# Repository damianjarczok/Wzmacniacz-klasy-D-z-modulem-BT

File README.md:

Wzmacniacz audio klasy D 2.1 oparty na TPA3116D2, z filtrem dolnoprzepustowym Sallen-Key, regulacją barwy (Baxandall), zasilaniem 24 V, interfejsem Bluetooth 4.2 (MH-M18) i wejściem AUX. Projekt PCB 4-warstwowy z filtracją EMI i optymalizacją ścieżek sygnałowych.

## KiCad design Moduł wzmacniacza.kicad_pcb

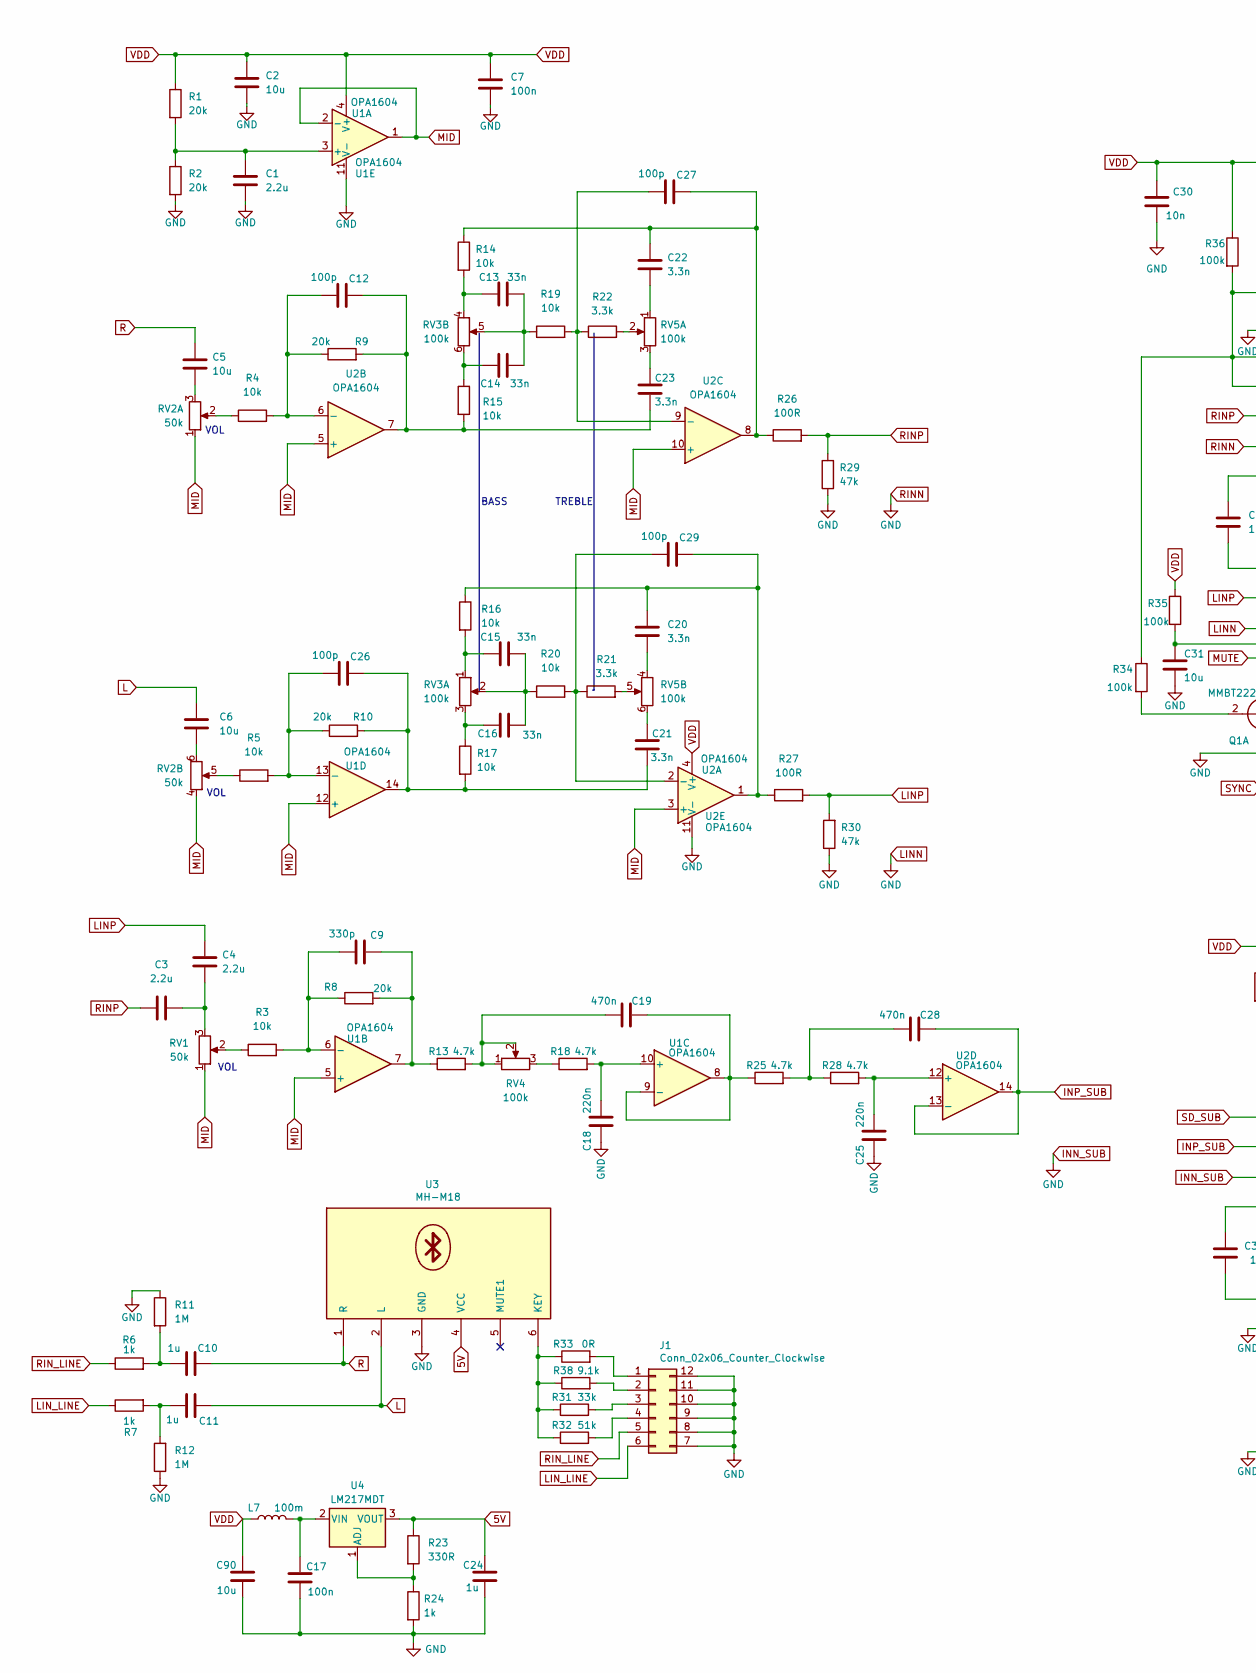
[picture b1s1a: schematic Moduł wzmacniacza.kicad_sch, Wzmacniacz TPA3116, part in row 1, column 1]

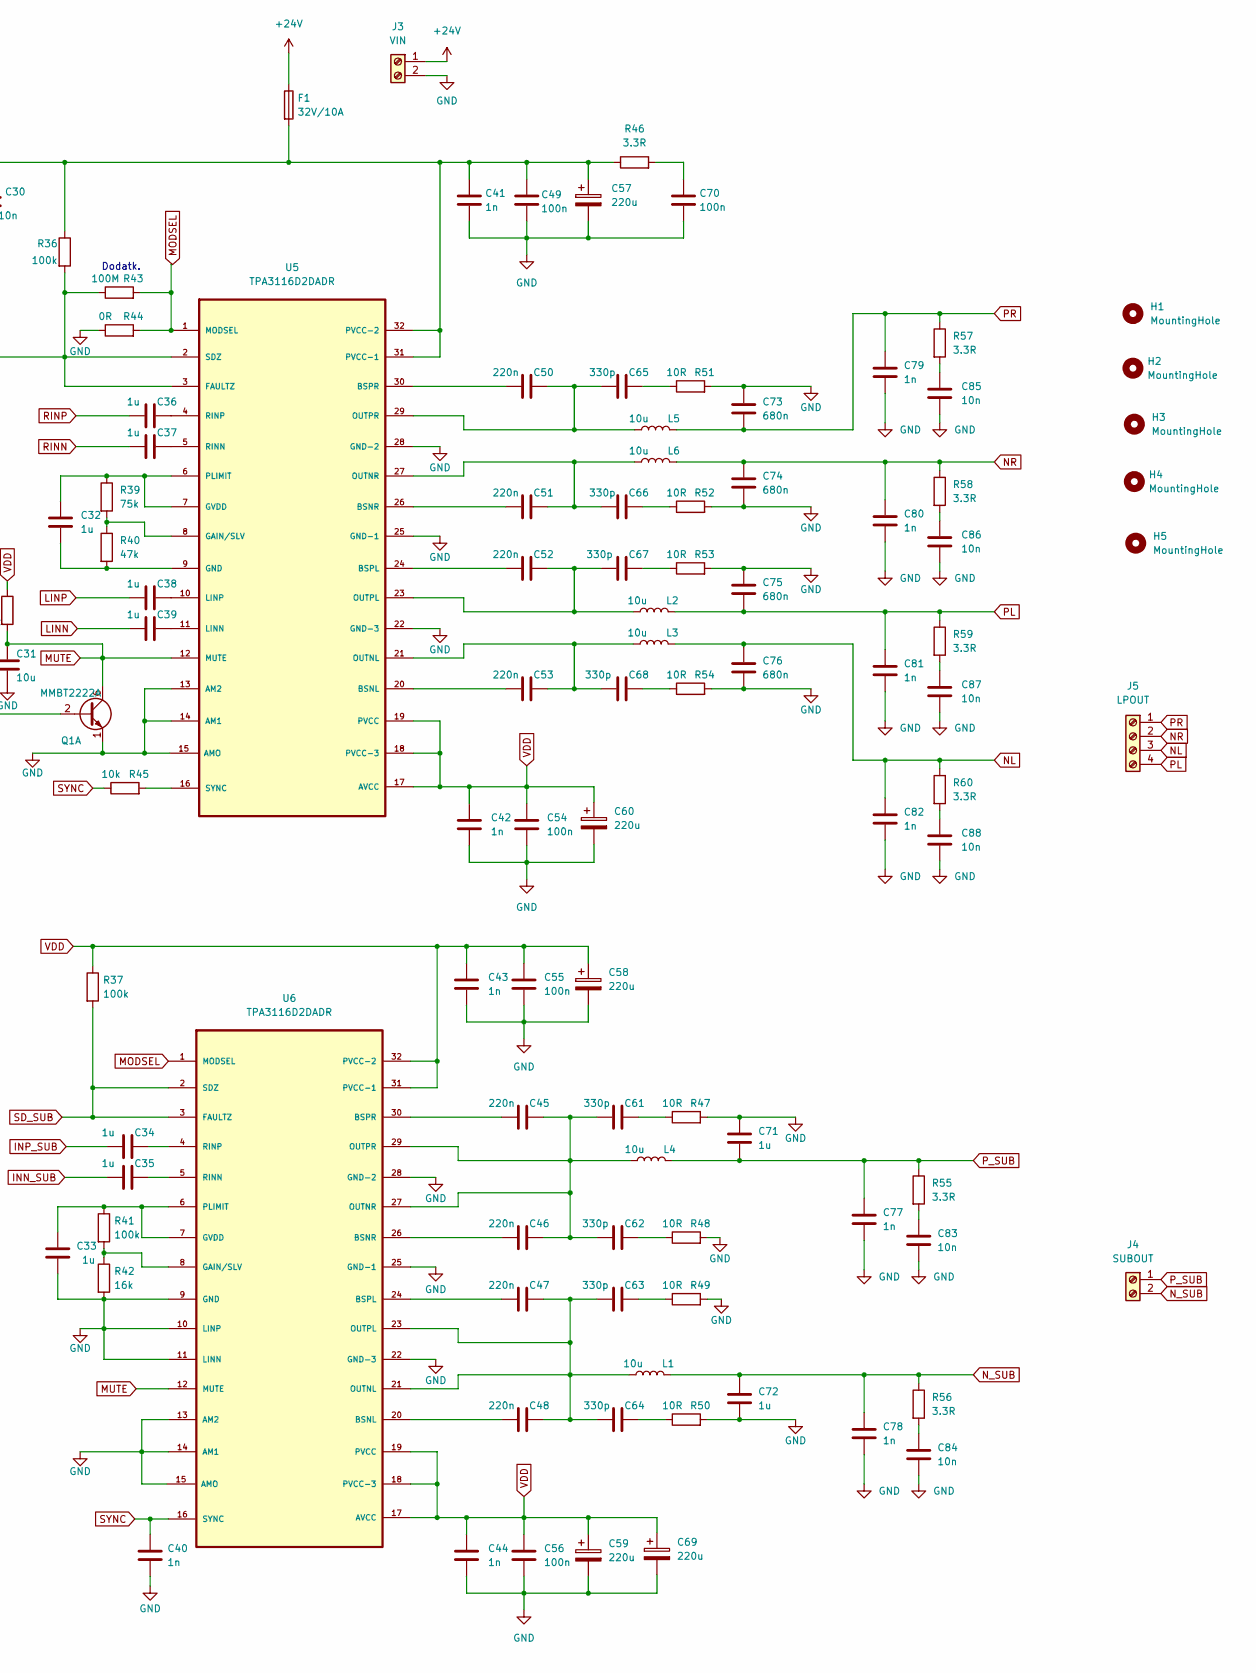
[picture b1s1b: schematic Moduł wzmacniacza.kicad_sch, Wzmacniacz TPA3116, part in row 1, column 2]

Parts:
C1, C3, C4: 2.2u; C_1206_3216Metric
C2, C5, C6, C31: 10u; C_1210_3225Metric
C7, C17, C49, C54, C55, C56, C70: 100n; C_1206_3216Metric
C9, C61, C62, C63, C64, C65, C66, C67, C68: 330p; C_0805_2012Metric
C10, C11, C34, C35, C36, C37, C38, C39, C71, C72: 1u; C_2220_5650Metric
C12, C26, C27, C29: 100p; C_0805_2012Metric
C13, C14, C15, C16: 33n; C_0805_2012Metric
C18, C25, C45, C46, C47, C48, C50, C51, C52, C53: 220n; C_0805_2012Metric
C19, C28: 470n; C_0805_2012Metric
C20, C21, C22, C23: 3.3n; C_0805_2012Metric
C24, C32, C33: 1u; C_1206_3216Metric
C30, C83, C84, C85, C86, C87, C88: 10n; C_1206_3216Metric
C40, C41, C42, C43, C44, C77, C78, C79, C80, C81, C82: 1n; C_0805_2012Metric
C57, C58, C59, C60, C69: 220u; CP_Elec_10x10
C73, C74, C75, C76: 680n; C_1206_3216Metric
C90: 10u; C_1206_3216Metric
F1: 32V/10A; Fuse
H1, H2, H3, H4, H5: MountingHole; MountingHole_3.2mm_M3_DIN965_Pad
J1: Conn_02x06_Counter_Clockwise; IDC-Header_2x06_P2.54mm_Vertical
J3: VIN; Screw 2
J4: SUBOUT; Screw 2
J5: LPOUT; Screw 4
L1, L2, L3, L4, L5, L6: 10u; Dlawik
L7: 100m; L_1812_4532Metric
Q1: MMBT2222A; SOT-23
R1, R2, R8, R9, R10: 20k; R_0805_2012Metric
R3, R4, R5, R14, R15, R16, R17, R19, R20, R45: 10k; R_0805_2012Metric
R6, R7, R24: 1k; R_0805_2012Metric
R11, R12: 1M; R_0805_2012Metric
R13, R18, R25, R28: 4.7k; R_0805_2012Metric
R21, R22: 3.3k; R_0805_2012Metric
R23: 330R; R_0805_2012Metric
R26, R27: 100R; R_0805_2012Metric
R29, R30, R40: 47k; R_0805_2012Metric
R31: 33k; R_0805_2012Metric
R32: 51k; R_0805_2012Metric
R33, R44: 0R; R_0805_2012Metric
R34, R35, R36, R37, R41: 100k; R_0805_2012Metric
R38: 9.1k; R_0805_2012Metric
R39: 75k; R_0805_2012Metric
R42: 16k; R_0805_2012Metric
R43: 100M; R_0805_2012Metric
R46, R55, R56, R57, R58, R59, R60: 3.3R; R_0805_2012Metric
R47, R48, R49, R50, R51, R52, R53, R54: 10R; R_0805_2012Metric
RV1: 50k; Pot single
RV2: 50k; Pot dual
RV3, RV5: 100k; Pot dual
RV4: 100k; Pot single
U1, U2: OPA1604; SOIC-14_3.9x8.7mm_P1.27mm
U3: MH-M18; BM20
U4: LM217MDT; TO-252-2
U5, U6: TPA3116D2DADR; HTSSOP-32-1EP_6.1x11mm_P0.65mm_EP5.2x11mm_Mask4.11x4.36mm

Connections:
5V: C24.1, R23.1, U3.4 (VCC), U4.3 (VOUT)
+24V: F1.1, J3.1
INN_SUB: C1.2, C2.2, C7.2, C17.2, C18.1, C24.2, C25.1, C30.2, C31.2, C33.2, C35.1, C37.1, C39.1, C40.2, C41.2, C42.2, C43.2, C44.2, C49.2, C54.2, C55.2, C56.2, C57.2, C58.2, C59.2, C60.2, C69.2, C70.2, C71.1, C72.2, C73.1, C74.2, C75.1, C76.2, C77.2, C78.2, C79.2, C80.2, C81.2, C82.2, C83.2, C84.2, C85.2, C86.2, C87.2, C88.2, C90.2, H1.1, H2.1, H3.1, H4.1, H5.1, J1.7, J1.8, J1.9, J1.10, J1.11, J1.12, J3.2, Q1.1 (E1), R2.2, R11.1, R12.1, R24.2, R29.1, R30.1, R42.2, R44.1, R47.2, R48.2, R49.2, R50.2, R51.2, R52.2, R53.2, R54.2, U1.11 (V-), U2.11 (V-), U3.3 (GND), U5.13 (AM2), U5.14 (AM1), U5.15 (AMO), U5.22 (GND-3), U5.25 (GND-1), U5.28 (GND-2), U5.33, U6.9 (GND), U6.10 (LINP), U6.11 (LINN), U6.13 (AM2), U6.14 (AM1), U6.15 (AMO), U6.22 (GND-3), U6.25 (GND-1), U6.28 (GND-2), U6.33
INP_SUB: C28.2, C34.1, U2.13 (-), U2.14
L: C6.1, C11.2, U3.2 (L)
LINP: C4.1, C38.1, R27.2, R30.2
LIN_LINE: J1.6, R7.1
MID: RV1.1, RV2.1, RV2.4, U1.1, U1.2 (-), U1.5 (+), U1.12 (+), U2.3 (+), U2.5 (+), U2.10 (+)
MODSEL: R43.2, R44.2, U5.1 (MODSEL), U6.1 (MODSEL)
MUTE: C31.1, Q1.6 (C1), R35.2, U5.12 (MUTE), U6.12 (MUTE)
NL: C76.1, C82.1, J5.3, L3.2, R60.1
NR: C74.1, C80.1, J5.2, L6.2, R58.1
N_SUB: C72.1, C78.1, J4.2, L1.2, R56.1
unnamed: C1.1, R1.2, R2.1, U1.3 (+)
unnamed: C3.2, C4.2, RV1.3
unnamed: C5.2, RV2.3
unnamed: C6.2, RV2.6
unnamed: C9.1, R3.2, R8.1, U1.6 (-)
unnamed: C9.2, R8.2, R13.1, U1.7
unnamed: C10.1, R6.2, R11.2
unnamed: C11.1, R7.2, R12.2
unnamed: C12.1, R4.2, R9.1, U2.6 (-)
unnamed: C12.2, C23.2, R9.2, R15.2, U2.7
unnamed: C13.1, R14.2, RV3.4
unnamed: C13.2, C14.2, R19.1, RV3.5
unnamed: C14.1, R15.1, RV3.6
unnamed: C15.1, R16.2, RV3.1
unnamed: C15.2, C16.2, R20.1, RV3.2
unnamed: C16.1, R17.1, RV3.3
unnamed: C17.1, L7.1, U4.2 (VIN)
unnamed: C18.2, R18.2, U1.10 (+)
unnamed: C19.1, R13.2, RV4.1, RV4.2
unnamed: C19.2, R25.1, U1.8, U1.9 (-)
unnamed: C20.1, C29.2, R16.1, R27.1, U2.1
unnamed: C20.2, RV5.4
unnamed: C21.1, RV5.6
unnamed: C21.2, C26.2, R10.2, R17.2, U1.14
unnamed: C22.1, C27.2, R14.1, R26.1, U2.8
unnamed: C22.2, RV5.1
unnamed: C23.1, RV5.3
unnamed: C25.2, R28.2, U2.12 (+)
unnamed: C26.1, R5.2, R10.1, U1.13 (-)
unnamed: C27.1, R19.2, R22.1, U2.9 (-)
unnamed: C28.1, R25.2, R28.1
unnamed: C29.1, R20.2, R21.1, U2.2 (-)
unnamed: C32.1, R39.1, U5.6 (PLIMIT), U5.7 (GVDD)
unnamed: C32.2, R40.2, U5.9 (GND)
unnamed: C33.1, R41.1, U6.6 (PLIMIT), U6.7 (GVDD)
unnamed: C34.2, U6.4 (RINP)
unnamed: C35.2, U6.5 (RINN)
unnamed: C36.2, U5.4 (RINP)
unnamed: C37.2, U5.5 (RINN)
unnamed: C38.2, U5.10 (LINP)
unnamed: C39.2, U5.11 (LINN)
unnamed: C45.1, U6.30 (BSPR)
unnamed: C45.2, C46.2, C61.1, C62.1, L4.1, U6.27 (OUTNR), U6.29 (OUTPR)
unnamed: C46.1, U6.26 (BSNR)
unnamed: C47.1, U6.24 (BSPL)
unnamed: C47.2, C48.2, C63.1, C64.1, L1.1, U6.21 (OUTNL), U6.23 (OUTPL)
unnamed: C48.1, U6.20 (BSNL)
unnamed: C50.1, U5.30 (BSPR)
unnamed: C50.2, C65.1, L5.1, U5.29 (OUTPR)
unnamed: C51.1, U5.26 (BSNR)
unnamed: C51.2, C66.1, L6.1, U5.27 (OUTNR)
unnamed: C52.1, U5.24 (BSPL)
unnamed: C52.2, C67.1, L2.1, U5.23 (OUTPL)
unnamed: C53.1, U5.20 (BSNL)
unnamed: C53.2, C68.1, L3.1, U5.21 (OUTNL)
unnamed: C61.2, R47.1
unnamed: C62.2, R48.1
unnamed: C63.2, R49.1
unnamed: C64.2, R50.1
unnamed: C65.2, R51.1
unnamed: C66.2, R52.1
unnamed: C67.2, R53.1
unnamed: C68.2, R54.1
unnamed: C70.1, R46.2
unnamed: C83.1, R55.2
unnamed: C84.1, R56.2
unnamed: C85.1, R57.2
unnamed: C86.1, R58.2
unnamed: C87.1, R59.2
unnamed: C88.1, R60.2
unnamed: J1.1, R33.2
unnamed: J1.2, R38.2
unnamed: J1.3, R31.2
unnamed: J1.4, R32.2
unnamed: Q1.2 (B1), R34.2
unnamed: R3.1, RV1.2
unnamed: R4.1, RV2.2
unnamed: R5.1, RV2.5
unnamed: R18.1, RV4.3
unnamed: R21.2, RV5.5
unnamed: R22.2, RV5.2
unnamed: R23.2, R24.1, U4.1 (ADJ)
unnamed: R31.1, R32.1, R33.1, R38.1, U3.6 (KEY)
unnamed: R34.1, R36.2, R43.1, U5.2 (SDZ), U5.3 (FAULTZ)
unnamed: R39.2, R40.1, U5.8 (GAIN/SLV)
unnamed: R41.2, R42.1, U6.8 (GAIN/SLV)
unnamed: R45.2, U5.16 (SYNC)
PL: C75.2, C81.1, J5.4, L2.2, R59.1
PR: C73.2, C79.1, J5.1, L5.2, R57.1
P_SUB: C71.2, C77.1, J4.1, L4.2, R55.1
R: C5.1, C10.2, U3.1 (R)
RINP: C3.1, C36.1, R26.2, R29.2
RIN_LINE: J1.5, R6.1
SD_SUB: R37.2, U6.2 (SDZ), U6.3 (FAULTZ)
SYNC: C40.1, R45.1, U6.16 (SYNC)
VDD: C2.1, C7.1, C30.1, C41.1, C42.1, C43.1, C44.1, C49.1, C54.1, C55.1, C56.1, C57.1, C58.1, C59.1, C60.1, C69.1, C90.1, F1.2, L7.2, R1.1, R35.1, R36.1, R37.1, R46.1, U1.4 (V+), U2.4 (V+), U5.17 (AVCC), U5.18 (PVCC-3), U5.19 (PVCC), U5.31 (PVCC-1), U5.32 (PVCC-2), U6.17 (AVCC), U6.18 (PVCC-3), U6.19 (PVCC), U6.31 (PVCC-1), U6.32 (PVCC-2)

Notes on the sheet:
VOL
TREBLE
Dodatk.
BASS

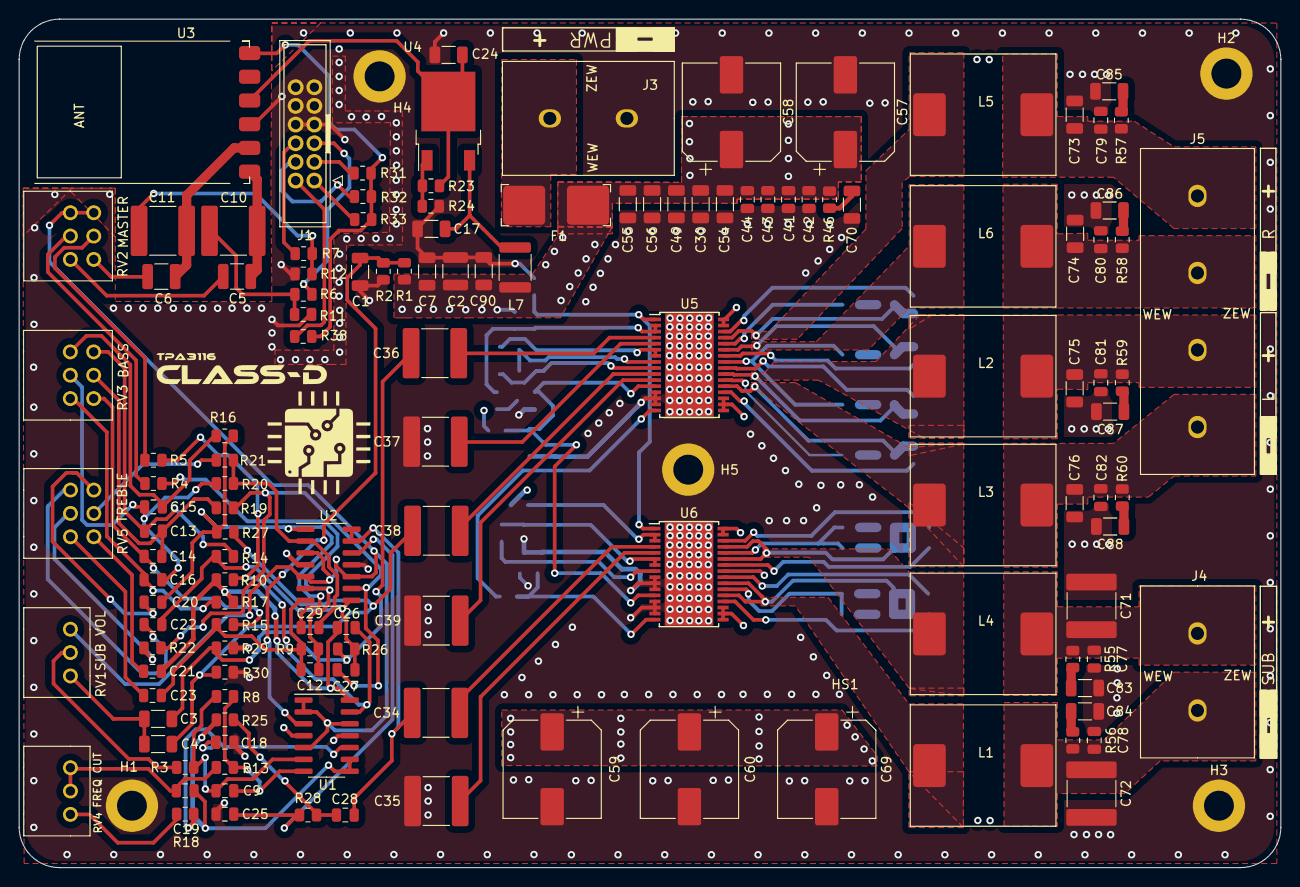
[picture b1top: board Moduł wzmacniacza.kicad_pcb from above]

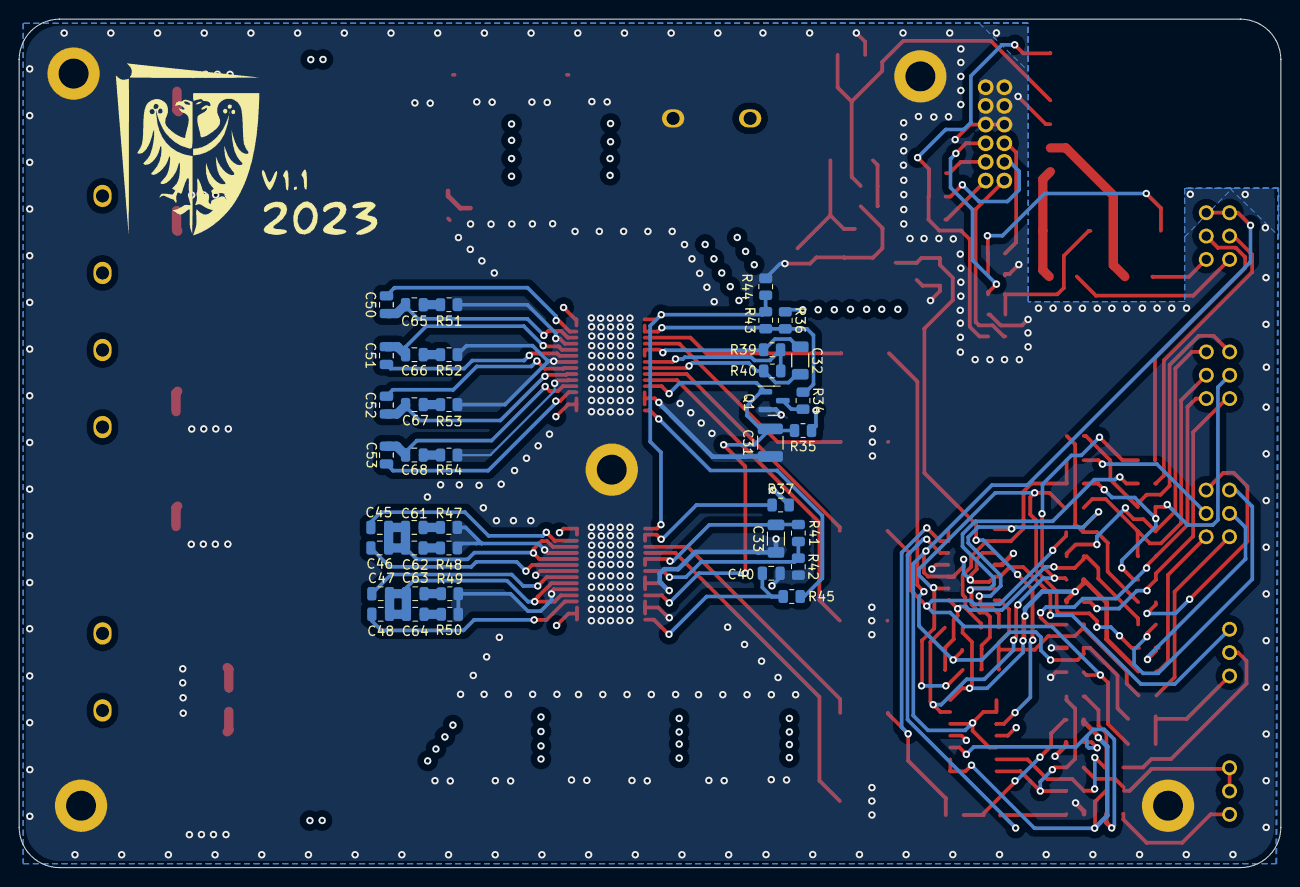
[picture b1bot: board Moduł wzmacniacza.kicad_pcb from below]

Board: 4 copper layers, 135.1 x 90.9 mm, 177 parts (40 on the bottom side), 109 nets.

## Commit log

2025-08-07 Create README.md
    Wzmacniacz audio klasy D 2.1 oparty na TPA3116D2, z filtrem dolnoprzepustowym Sallen-Key, regulacją barwy (Baxandall), zasilaniem 24 V, interfejsem Bluetooth 4.2 (MH-M18) i wejściem AUX. Projekt PCB 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
